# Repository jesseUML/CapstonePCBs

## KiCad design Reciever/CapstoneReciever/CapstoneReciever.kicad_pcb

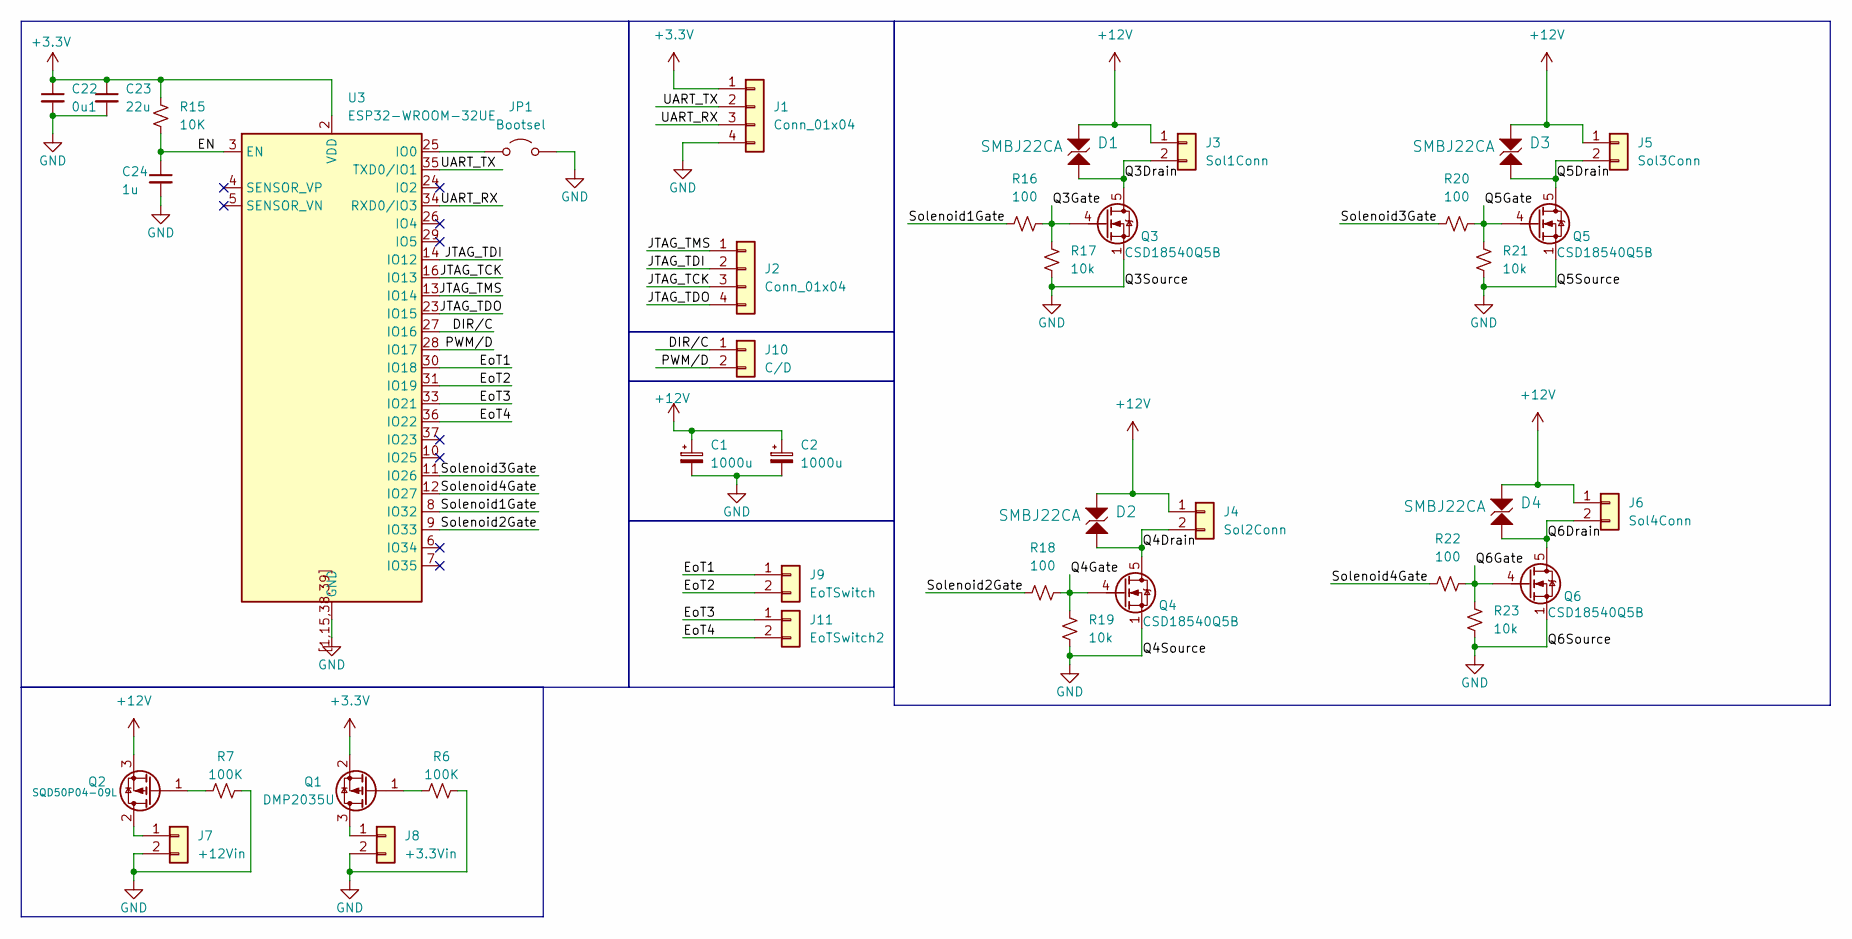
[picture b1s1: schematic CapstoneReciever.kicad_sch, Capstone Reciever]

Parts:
C1, C2: 1000u; CP_Elec_10x14.3
C22: 0u1; C_0402_1005Metric
C23: 22u; C_0603_1608Metric
C24: 1u; C_0603_1608Metric
D1, D2, D3, D4: SMBJ22CA; D_SMB; Voltage 22V; Part Description Bi-directional Transient Voltage Suppre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
J1, J2: Conn_01x04; PinHeader_1x04_P2.54mm_Vertical
J3: Sol1Conn; TerminalBlock_CUI_TB007-508-02_1x02_P5.08mm_Horizontal
J4: Sol2Conn; TerminalBlock_CUI_TB007-508-02_1x02_P5.08mm_Horizontal
J5: Sol3Conn; TerminalBlock_CUI_TB007-508-02_1x02_P5.08mm_Horizontal
J6: Sol4Conn; TerminalBlock_CUI_TB007-508-02_1x02_P5.08mm_Horizontal
J7: +12Vin; TerminalBlock_CUI_TB007-508-02_1x02_P5.08mm_Horizontal
J8: +3.3Vin; TerminalBlock_CUI_TB007-508-02_1x02_P5.08mm_Horizontal
J9: EoTSwitch; TerminalBlock_CUI_TB007-508-02_1x02_P5.08mm_Horizontal
J10: C/D; TerminalBlock_CUI_TB007-508-02_1x02_P5.08mm_Horizontal
J11: EoTSwitch2; TerminalBlock_CUI_TB007-508-02_1x02_P5.08mm_Horizontal
JP1: Bootsel; PinHeader_1x02_P2.54mm_Vertical
Q1: DMP2035U; SOT-23
Q2: SQD50P04-09L; TO-252-3_TabPin2
Q3, Q4, Q5, Q6: CSD18540Q5B; TDSON-8-1
R6, R7: 100K; R_0603_1608Metric
R15: 10K; R_0603_1608Metric
R16, R18, R20, R22: 100; R_0603_1608Metric
R17, R19, R21, R23: 10k; R_0603_1608Metric
U3: ESP32-WROOM-32UE

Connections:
+3.3V: C22.1, C23.1, J1.1, Q1.2 (S), R15.1, U3.2 (VDD)
+12V: C1.1, C2.1, D1.2, D2.2, D3.2, D4.2, J3.1, J4.1, J5.1, J6.1, Q2.3 (S)
/DIR/C: J10.1, U3.27 (IO16)
/EN: C24.1, R15.2, U3.3 (EN)
/EoT1: J9.1, U3.30 (IO18)
/EoT2: J9.2, U3.31 (IO19)
/EoT3: J11.1, U3.33 (IO21)
/EoT4: J11.2, U3.36 (IO22)
/JTAG_TCK: J2.3, U3.16 (IO13)
/JTAG_TDI: J2.2, U3.14 (IO12)
/JTAG_TDO: J2.4, U3.23 (IO15)
/JTAG_TMS: J2.1, U3.13 (IO14)
/PWM/D: J10.2, U3.28 (IO17)
/Q3Drain: D1.1, J3.2, Q3.5 (D)
/Q3Gate: Q3.4 (G), R16.2, R17.1
/Q4Drain: D2.1, J4.2, Q4.5 (D)
/Q4Gate: Q4.4 (G), R18.2, R19.1
/Q5Drain: D3.1, J5.2, Q5.5 (D)
/Q5Gate: Q5.4 (G), R20.2, R21.1
/Q6Drain: D4.1, J6.2, Q6.5 (D)
/Q6Gate: Q6.4 (G), R22.2, R23.1
/Solenoid1Gate: R16.1, U3.8 (IO32)
/Solenoid2Gate: R18.1, U3.9 (IO33)
/Solenoid3Gate: R20.1, U3.11 (IO26)
/Solenoid4Gate: R22.1, U3.12 (IO27)
/UART_RX: J1.3, U3.34 (RXD0/IO3)
/UART_TX: J1.2, U3.35 (TXD0/IO1)
GND: C1.2, C2.2, C22.2, C23.2, C24.2, J1.4, J7.2, J8.2, JP1.2 (B), Q3.1 (S), Q3.2 (S), Q3.3 (S), Q4.1 (S), Q4.2 (S), Q4.3 (S), Q5.1 (S), Q5.2 (S), Q5.3 (S), Q6.1 (S), Q6.2 (S), Q6.3 (S), R6.2, R7.2, R17.2, R19.2, R21.2, R23.2, U3.1 (GND), U3.15 (GND), U3.38 (GND), U3.39 (GND), U3.[1,15,38,39] (GND); also elsewhere on the board
unnamed: J7.1, Q2.2 (D)
unnamed: J8.1, Q1.3 (D)
unnamed: JP1.1 (A), U3.25 (IO0)
unnamed: Q1.1 (G), R6.1
unnamed: Q2.1 (G), R7.1

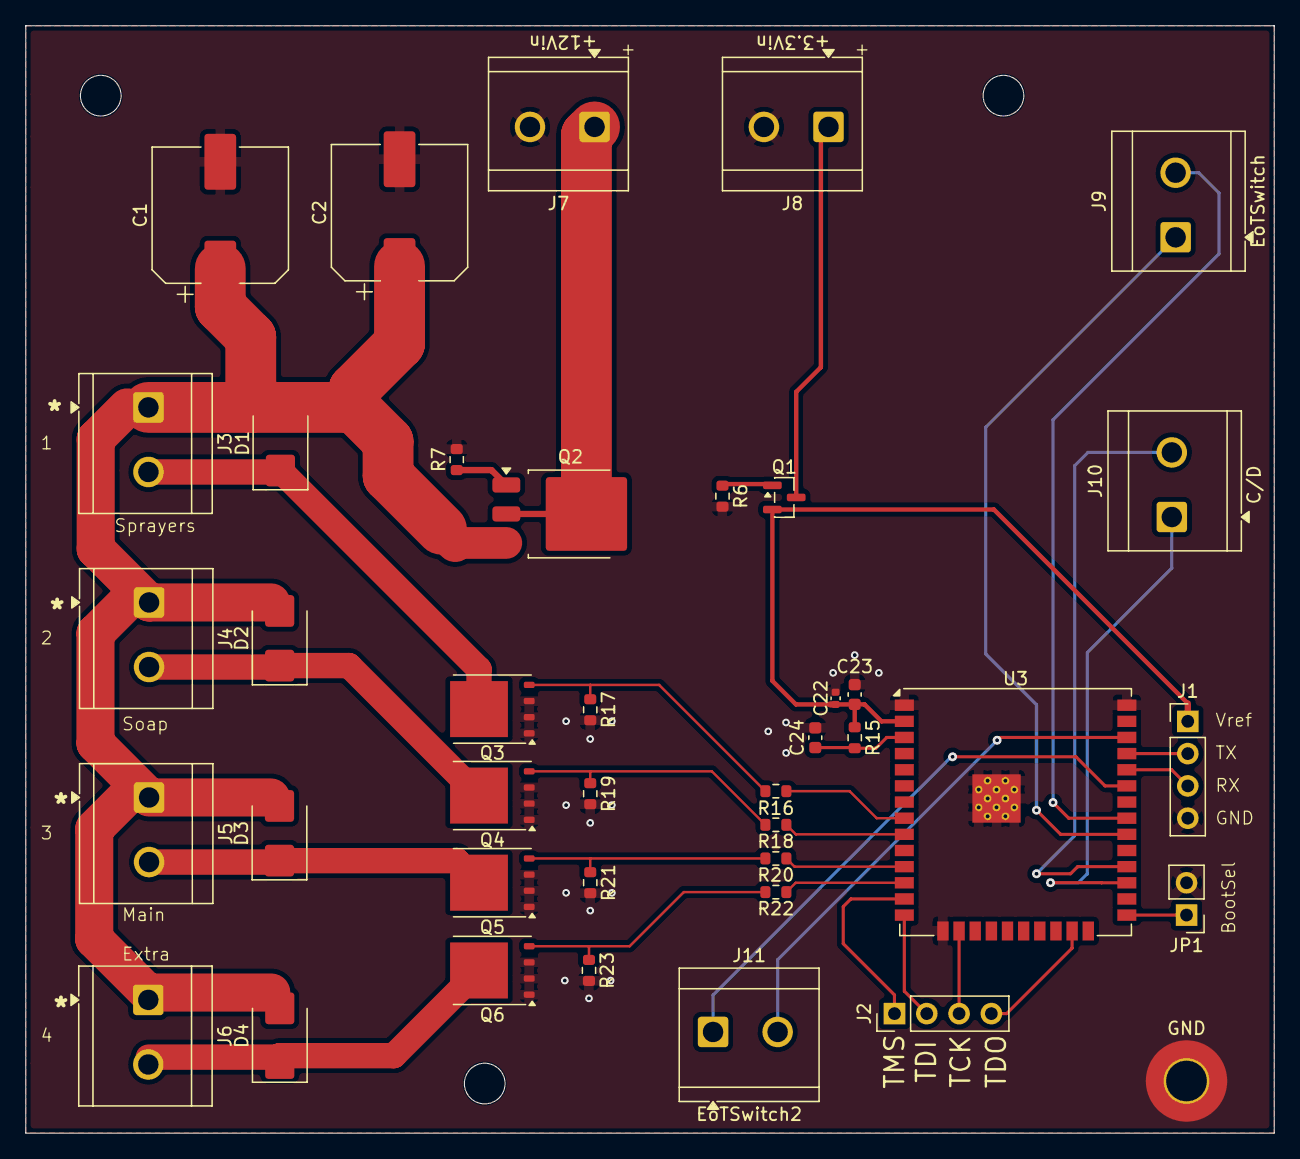
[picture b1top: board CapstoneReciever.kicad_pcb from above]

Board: 4 copper layers, 98.2 x 87.1 mm, 40 parts (0 on the bottom side), 33 nets.

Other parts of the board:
GND: MountingHole_3.2mm_M3_Pad_TopOnly

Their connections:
GND: GND.1; also elsewhere on the board

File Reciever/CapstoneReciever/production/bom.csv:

Designator,Footprint,Quantity,Value,LCSC Part #
"C1, C2",CP_Elec_10x14.3,2,1000u,
C22,0402,1,0u1,
C23,0603,1,22u,
C24,0603,1,1u,
"D1, D2, D3, D4",D_SMB,4,SMBJ22CA,
"J1, J2",PinHeader_1x04_P2.54mm_Vertical,2,Conn_01x04,
J10,TerminalBlock_CUI_TB007-508-02_1x02_P5.08mm_Horizontal,1,C/D,
J11,TerminalBlock_CUI_TB007-508-02_1x02_P5.08mm_Horizontal,1,EoTSwitch2,
J3,TerminalBlock_CUI_TB007-508-02_1x02_P5.08mm_Horizontal,1,Sol1Conn,
J4,TerminalBlock_CUI_TB007-508-02_1x02_P5.08mm_Horizontal,1,Sol2Conn,
J5,TerminalBlock_CUI_TB007-508-02_1x02_P5.08mm_Horizontal,1,Sol3Conn,
J6,TerminalBlock_CUI_TB007-508-02_1x02_P5.08mm_Horizontal,1,Sol4Conn,
J7,TerminalBlock_CUI_TB007-508-02_1x02_P5.08mm_Horizontal,1,+12Vin,
J8,TerminalBlock_CUI_TB007-508-02_1x02_P5.08mm_Horizontal,1,+3.3Vin,
J9,TerminalBlock_CUI_TB007-508-02_1x02_P5.08mm_Horizontal,1,EoTSwitch,
JP1,PinHeader_1x02_P2.54mm_Vertical,1,Bootsel,
Q1,SOT-23,1,DMP2035U,
Q2,TO-252-3_TabPin2,1,SQD50P04-09L,
"Q3, Q4, Q5, Q6",TDSON-8-1,4,CSD18540Q5B,
"R15, R17, R19, R21, R23",0603,5,10K,
"R16, R18, R20, R22",0603,4,100,
"R6, R7",0603,2,100K,
U3,ESP32-WROOM-32UE,1,ESP32-WROOM-32UE,

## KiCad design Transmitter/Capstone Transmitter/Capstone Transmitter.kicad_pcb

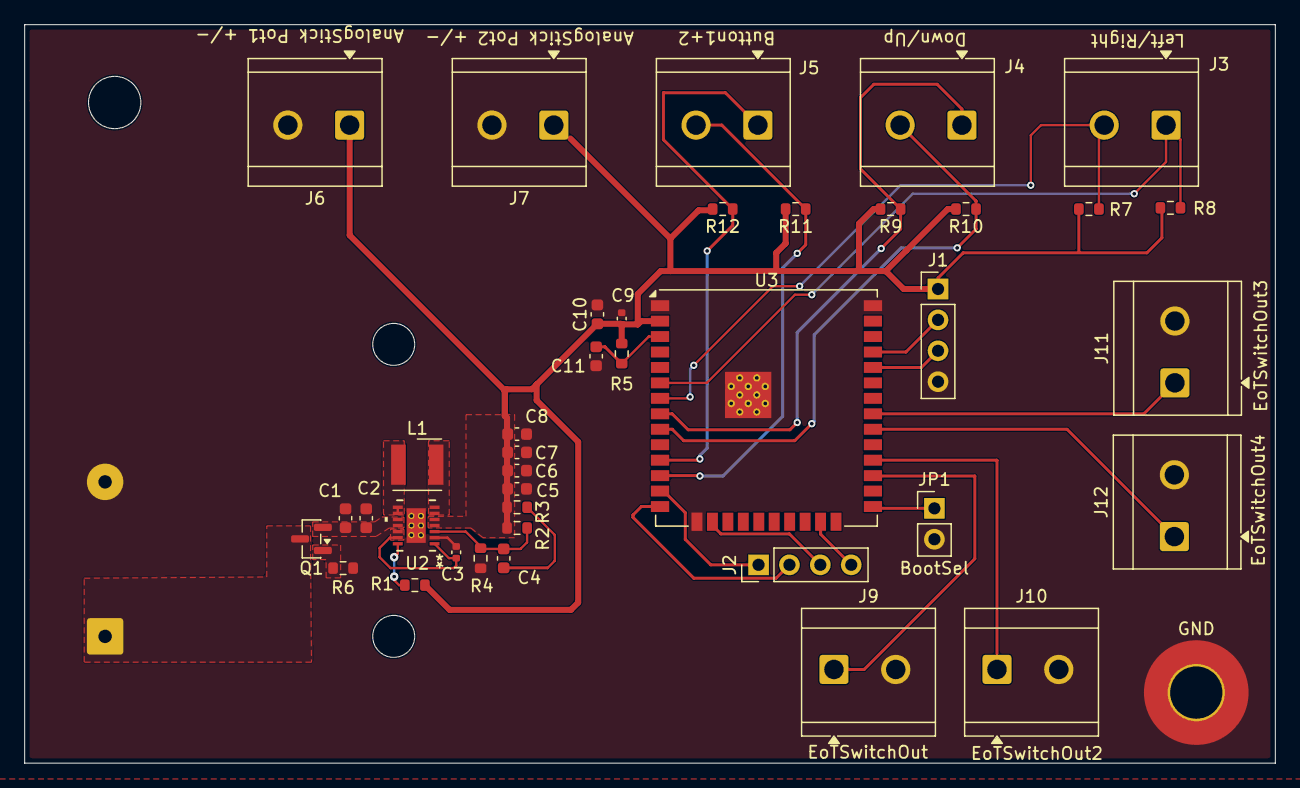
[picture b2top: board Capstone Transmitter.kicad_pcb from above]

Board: 4 copper layers, 102.8 x 60.7 mm, 41 parts (1 on the bottom side), 29 nets.

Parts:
BT1: Battery; BatteryHolder_Keystone_2479_3xAAA
C1, C2: 10u; C_0603_1608Metric
C3: 100n; C_0402_1005Metric
C4: 4p7; C_0603_1608Metric
C5, C6, C7, C8, C10: 22u; C_0603_1608Metric
C9: 0u1; C_0402_1005Metric
C11: 1u; C_0603_1608Metric
GND: MountingHole_4.3mm_M4_Pad_TopOnly
J1, J2: Conn_01x04; PinHeader_1x04_P2.54mm_Vertical
J3: Left/Right; TerminalBlock_CUI_TB007-508-02_1x02_P5.08mm_Horizontal
J4: Down/Up; TerminalBlock_CUI_TB007-508-02_1x02_P5.08mm_Horizontal
J5: Button1+2; TerminalBlock_CUI_TB007-508-02_1x02_P5.08mm_Horizontal
J6: AnalogStick Pot1 +/-; TerminalBlock_CUI_TB007-508-02_1x02_P5.08mm_Horizontal
J7: AnalogStick Pot2 +/-; TerminalBlock_CUI_TB007-508-02_1x02_P5.08mm_Horizontal
J9: EoTSwitchOut; TerminalBlock_CUI_TB007-508-02_1x02_P5.08mm_Horizontal
J10: EoTSwitchOut2; TerminalBlock_CUI_TB007-508-02_1x02_P5.08mm_Horizontal
J11: EoTSwitchOut3; TerminalBlock_CUI_TB007-508-02_1x02_P5.08mm_Horizontal
J12: EoTSwitchOut4; TerminalBlock_CUI_TB007-508-02_1x02_P5.08mm_Horizontal
JP1: BootSel; PinHeader_1x02_P2.54mm_Vertical
L1: 1u; L_Wurth_WE-LQSH-4020
Q1: DMP2035U; SOT-23
R1, R2: 1M; R_0603_1608Metric
R3: 68K; R_0603_1608Metric
R4: 180K; R_0603_1608Metric
R5, R7, R8, R9, R10, R11, R12: 10K; R_0603_1608Metric
R6: 100K; R_0603_1608Metric
U2: TPS63020DSJR; DSJ14_2P85X1P58
U3: ESP32-WROOM-32UE

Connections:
+3.3V: C5.1, C6.1, C7.1, C8.1, C9.1, C10.1, J1.1, J6.1, J7.1, R1.2, R2.1, R3.1, R5.1, R7.2, R8.2, R9.2, R10.2, R11.2, R12.2, U2.4 (VOUT), U2.5 (VOUT), U3.2 (VDD)
/EN: C3.1, U2.1 (VINA), U2.12 (EN), U2.13 (PS/SYNC)
/EN2: C11.1, R5.2, U3.3 (EN)
/EoTLED1: J9.1, U3.27 (IO16)
/EoTLED2: J10.1, U3.28 (IO17)
/EoTLED3: J11.1, U3.31 (IO19)
/EoTLED4: J12.1, U3.30 (IO18)
/FB: C4.2, R2.2, R4.1, U2.3 (FB)
/JOY_BTN1: J5.2, R11.1, U3.12 (IO27)
/JOY_BTN2: J5.1, R12.1, U3.11 (IO26)
/JOY_DOWN: J4.1, R9.1, U3.8 (IO32)
/JOY_UP: J4.2, R10.1, U3.9 (IO33)
/JOY_X/LEFT: J3.1, R8.1, U3.6 (IO34)
/JOY_Y/RIGHT: J3.2, R7.1, U3.7 (IO35)
/JTAG_TCK: J2.3, U3.16 (IO13)
/JTAG_TDI: J2.2, U3.14 (IO12)
/JTAG_TDO: J2.4, U3.23 (IO15)
/JTAG_TMS: J2.1, U3.13 (IO14)
/L1: L1.1, U2.8 (L1), U2.9 (L1)
/L2: L1.2, U2.6 (L2), U2.7 (L2)
/UART_RX: J1.3, U3.34 (RXD0/IO3)
/UART_TX: J1.2, U3.35 (TXD0/IO1)
GND: BT1.2 (-), C1.2, C2.2, C3.2, C5.2, C6.2, C7.2, C8.2, C9.2, C10.2, C11.2, GND.1, J1.4, J6.2, J7.2, J9.2, J10.2, J11.2, J12.2, JP1.2 (B), R4.2, R6.2, U2.2 (GND), U2.15 (EPAD), U3.1 (GND), U3.15 (GND), U3.38 (GND), U3.39 (GND)
unnamed: BT1.1 (+), Q1.3 (D)
unnamed: C4.1, R3.2
unnamed: JP1.1 (A), U3.25 (IO0)
unnamed: Q1.1 (G), R6.1
unnamed: R1.1, U2.14 (PG)
VBAT: C1.1, C2.1, Q1.2 (S), U2.10 (VIN), U2.11 (VIN)

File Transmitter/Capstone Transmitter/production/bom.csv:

Designator,Footprint,Quantity,Value,LCSC Part #
BT1,BatteryHolder_Keystone_2479_3xAAA,1,Battery,
"C1, C2",0603,2,10u,
"C10, C5, C6, C7, C8",0603,5,22u,
C11,0603,1,1u,
C3,0402,1,100n,
C4,0603,1,4p7,
C9,0402,1,0u1,
"J1, J2",PinHeader_1x04_P2.54mm_Vertical,2,Conn_01x04,
J10,TerminalBlock_CUI_TB007-508-02_1x02_P5.08mm_Horizontal,1,EoTSwitchOut2,
J11,TerminalBlock_CUI_TB007-508-02_1x02_P5.08mm_Horizontal,1,EoTSwitchOut3,
J12,TerminalBlock_CUI_TB007-508-02_1x02_P5.08mm_Horizontal,1,EoTSwitchOut4,
J3,TerminalBlock_CUI_TB007-508-02_1x02_P5.08mm_Horizontal,1,Left/Right,
J4,TerminalBlock_CUI_TB007-508-02_1x02_P5.08mm_Horizontal,1,Down/Up,
J5,TerminalBlock_CUI_TB007-508-02_1x02_P5.08mm_Horizontal,1,Button1+2,
J6,TerminalBlock_CUI_TB007-508-02_1x02_P5.08mm_Horizontal,1,AnalogStick Pot1 +/-,
J7,TerminalBlock_CUI_TB007-508-02_1x02_P5.08mm_Horizontal,1,AnalogStick Pot2 +/-,
J9,TerminalBlock_CUI_TB007-508-02_1x02_P5.08mm_Horizontal,1,EoTSwitchOut,
JP1,PinHeader_1x02_P2.54mm_Vertical,1,BootSel,
L1,L_Wurth_WE-LQSH-4020,1,1u,
Q1,SOT-23,1,DMP2035U,
"R1, R2",0603,2,1M,
"R10, R11, R12, R5, R7, R8, R9",0603,7,10K,
R3,0603,1,68K,
R4,0603,1,180K,
R6,0603,1,100K,
U2,DSJ14_2P85X1P58,1,TPS63020DSJR,
U3,ESP32-WROOM-32UE,1,ESP32-WROOM-32UE,
